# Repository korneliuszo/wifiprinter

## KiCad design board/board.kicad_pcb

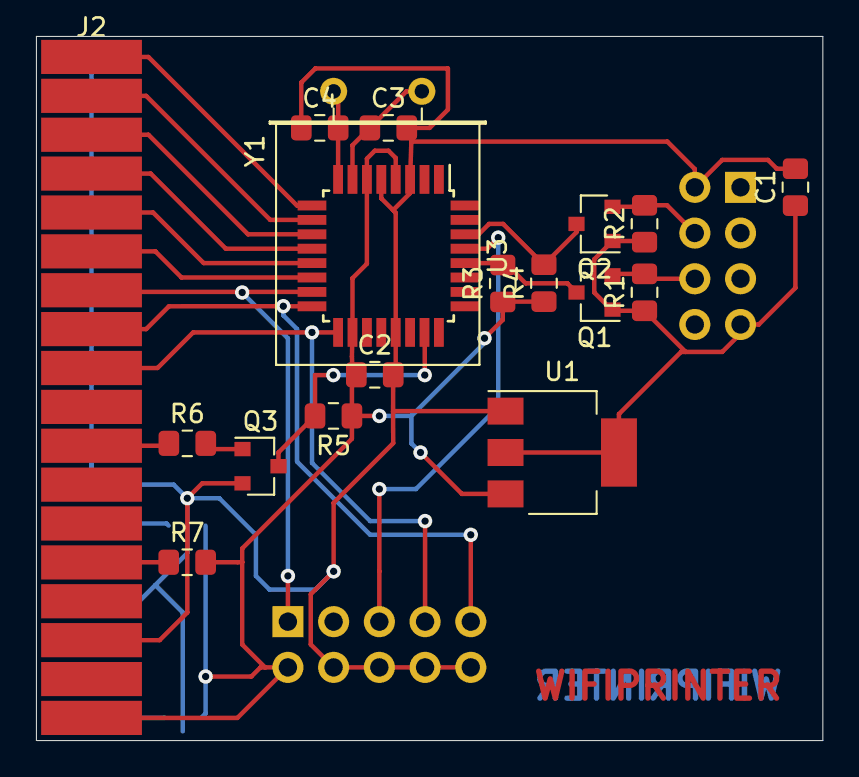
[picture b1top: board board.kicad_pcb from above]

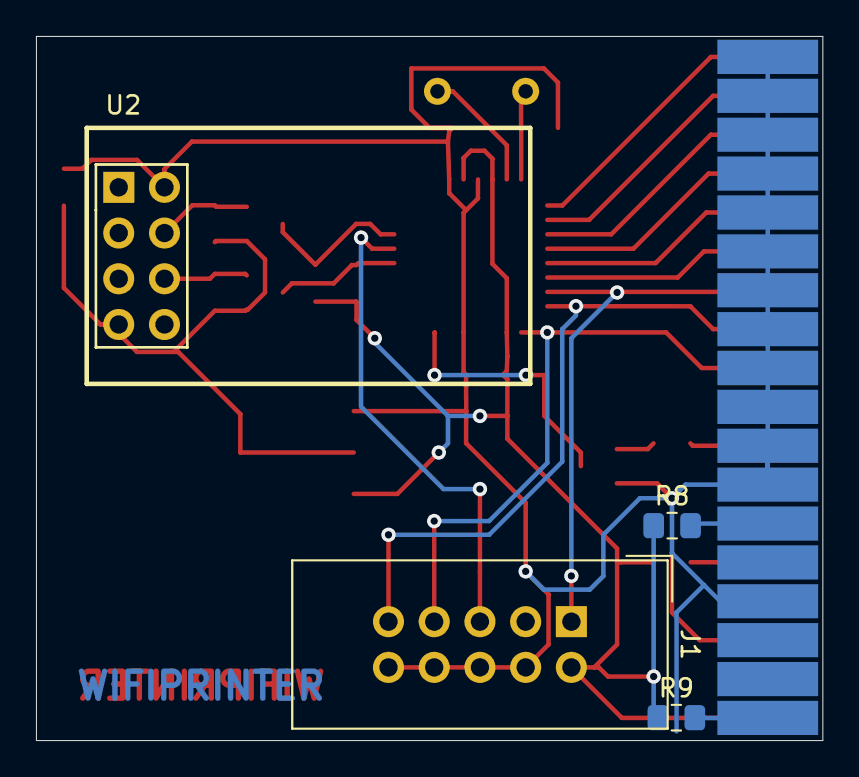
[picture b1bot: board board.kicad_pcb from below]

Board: 2 copper layers, 43.7 x 39.1 mm, 22 parts (4 on the bottom side), 25 nets.

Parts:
C1, C2: 100n; C_0805_2012Metric_Pad1.15x1.40mm_HandSolder
C3, C4: 22p; C_0805_2012Metric_Pad1.15x1.40mm_HandSolder
J1: AVR-ISP-10; IDC-Header_2x05_P2.54mm_Vertical
J2: Conn_02x18_Top_Bottom; Centronics 36
Q1, Q2: BSS138; SOT-23
Q3: BC847; SOT-23
R1, R2, R3, R4, R5, R6, R7, R8, R9: 10k; R_0805_2012Metric_Pad1.15x1.40mm_HandSolder
U1: AP1117-33; SOT-223-3_TabPin2
U2: ESP-01v090; ESP-01
U3: ATmega328P-AU; TQFP-32_7x7mm_P0.8mm
Y1: 16MHz; Crystal_HC49-U_Horizontal

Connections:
+3V3: C1.1, Q1.1, Q2.1, R1.1, R2.1, U1.2, U2.7
+5V: C2.1, J1.2, J2.18, R3.1, R4.1, R5.1, R7.2, R8.1, R9.1, U1.3, U3.4, U3.6, U3.18
BUSY: Q3.3, R5.2, U3.23
D0: J2.2, U3.10
D1: J2.3, U3.11
D2: J2.4, U3.12
D3: J2.5, U3.13
D4: J2.6, U3.14
D5: J1.1, J2.7, U3.15
D6: J1.9, J2.8, U3.16
D7: J1.7, J2.9, U3.17
GND: C1.2, C2.2, C3.2, C4.1, J1.4, J1.6, J1.8, J1.10, J2.16, J2.19, J2.20, J2.21, J2.22, J2.23, J2.24, J2.25, J2.26, J2.27, J2.28, J2.29, J2.30, J2.33, Q3.2, U1.1, U2.2, U3.3, U3.5, U3.21
unnamed: C3.1, U3.7, Y1.2
unnamed: C4.2, U3.8, Y1.1
unnamed: J1.5, U3.29
unnamed: J2.11, R6.1
unnamed: J2.14, R7.1
unnamed: J2.31, R8.2
unnamed: J2.36, R9.2
unnamed: Q1.2, R1.2, U2.6
unnamed: Q1.3, R3.2, U3.28
unnamed: Q2.2, R2.2, U2.4
unnamed: Q2.3, R4.2, U3.30
unnamed: Q3.1, R6.2
STROBE: J2.1, U3.9

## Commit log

2020-06-09 Add initial board drawing
2020-06-09 Automatically connect to wifi
2020-06-09 Add gitignore
2020-06-21 Add esp code
2020-06-21 Add atmega portion of code
2020-06-21 Add more to gitignore
2020-06-21 Disable AP on boot
2020-06-21 Create LICENSE
2020-06-21 Use 16MHz crystal on schematics
2020-06-21 Add schematics in pdf
2020-06-22 Close socket on both ends
